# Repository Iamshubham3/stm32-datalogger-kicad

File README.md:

# STM32 Datalogger PCB (KiCad)

This project started from an STM32 dev-board baseline and was extended into a datalogger-oriented PCB.
Main additions: external EEPROM (I2C), LSE crystal for RTC accuracy, and backup cell support to keep RTC running when main power is off.

## What I changed (conversion summary)
- Added I2C EEPROM block (address pins, decoupling, write-protect as applicable)
- Added I2C pull-up resistors sized for 3.3V logic
- Added 32.768 MHz crystal (LSE) for stable RTC timekeeping
- Added backup power cell circuitry (VBAT/RTC domain support)
- Updated connectors/test points for logging/debug (UART/I2C as required)
- Verified ERC/DRC and updated net labels + power domains

## Datalogger use-case
- Logs sensor/measurement data via I2C/SPI/UART peripherals
- Stores samples into EEPROM and timestamps using RTC (battery-backed)

## Tools
- KiCad v8

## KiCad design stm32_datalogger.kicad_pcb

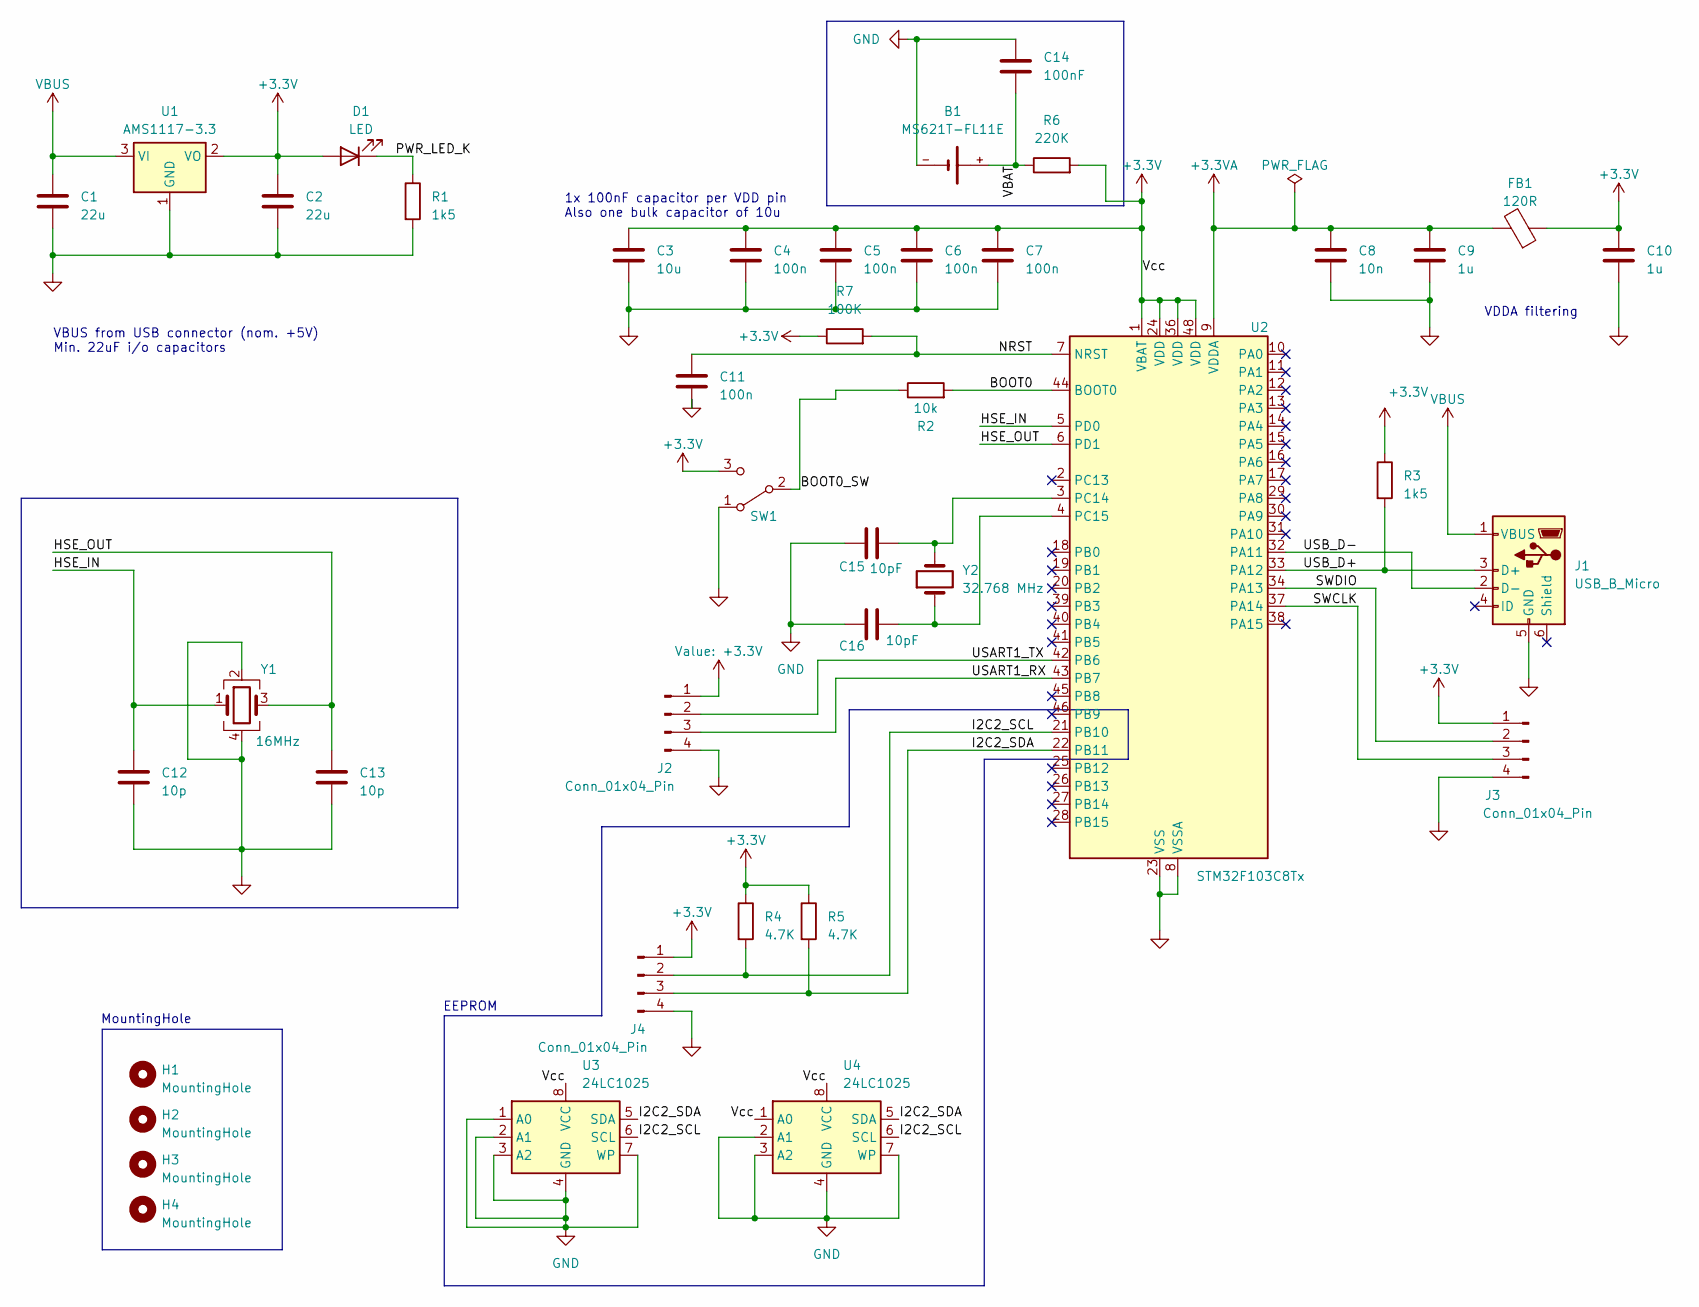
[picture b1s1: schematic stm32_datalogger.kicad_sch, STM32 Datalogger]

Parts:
B1: MS621T-FL11E; MS621FE-FL11E
C1, C2: 22u; C_0805_2012Metric
C3: 10u; C_0603_1608Metric
C4, C5, C6, C7, C11: 100n; C_0402_1005Metric
C8: 10n; C_0402_1005Metric
C9, C10: 1u; C_0402_1005Metric
C12, C13: 10p; C_0402_1005Metric
C14: 100nF; C_0402_1005Metric
C15, C16: 10pF; C_0402_1005Metric
D1: LED; LED_0603_1608Metric
FB1: 120R; L_0603_1608Metric
H1, H2, H3, H4: MountingHole; MountingHole_2.2mm_M2
J1: USB_B_Micro; USB_Micro-B_Wuerth_629105150521
J2, J3, J4: Conn_01x04_Pin; PinHeader_1x04_P2.54mm_Vertical
R1, R3: 1k5; R_0402_1005Metric
R2: 10k; R_0402_1005Metric
R4, R5: 4.7K; R_0402_1005Metric
R6: 220K; R_0402_1005Metric
R7: 100K; R_0402_1005Metric
SW1: SW_SPDT; SW_SPDT_PCM12
U1: AMS1117-3.3; SOT-223-3_TabPin2
U2: STM32F103C8Tx; LQFP-48_7x7mm_P0.5mm
U3, U4: 24LC1025; SOIC-8_3.9x4.9mm_P1.27mm
Y1: 16MHz; Crystal_SMD_3225-4Pin_3.2x2.5mm
Y2: 32.768 MHz; Crystal_SMD_3215-2Pin_3.2x1.5mm

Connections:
+3.3V: C2.1, C3.1, C4.1, C5.1, C6.1, C7.1, C10.1, D1.2 (A), FB1.1, J2.1, J3.1, J4.1, R3.1, R4.1, R5.1, R6.2, R7.1, SW1.3 (C), U1.2 (VO), U2.1 (VBAT), U2.24 (VDD), U2.36 (VDD), U2.48 (VDD), U3.8 (VCC), U4.1 (A0), U4.8 (VCC)
+3.3VA: C8.1, C9.1, FB1.2, U2.9 (VDDA)
/BOOT0: R2.2, U2.44 (BOOT0)
/BOOT0_SW: R2.1, SW1.2 (B)
/HSE_IN: C12.1, U2.5 (PD0), Y1.1
/HSE_OUT: C13.1, U2.6 (PD1), Y1.3
/I2C2_SCL: J4.2, R4.2, U2.21 (PB10), U3.6 (SCL), U4.6 (SCL)
/I2C2_SDA: J4.3, R5.2, U2.22 (PB11), U3.5 (SDA), U4.5 (SDA)
/NRST: C11.1, R7.2, U2.7 (NRST)
/PWR_LED_K: D1.1 (K), R1.1
/SWCLK: J3.3, U2.37 (PA14)
/SWDIO: J3.2, U2.34 (PA13)
/USART1_RX: J2.3, U2.43 (PB7)
/USART1_TX: J2.2, U2.42 (PB6)
/USB_D+: J1.3 (D+), R3.2, U2.33 (PA12)
/USB_D-: J1.2 (D-), U2.32 (PA11)
/VBAT: B1.+, C14.2, R6.1
GND: B1.-, C1.2, C2.2, C3.2, C4.2, C5.2, C6.2, C7.2, C8.2, C9.2, C10.2, C11.2, C12.2, C13.2, C14.1, C15.1, C16.1, J1.5 (GND), J2.4, J3.4, J4.4, R1.2, SW1.1 (A), U1.1 (GND), U2.8 (VSSA), U2.23 (VSS), U2.35 (VSS), U2.47 (VSS), U3.1 (A0), U3.2 (A1), U3.3 (A2), U3.4 (GND), U3.7 (WP), U4.2 (A1), U4.3 (A2), U4.4 (GND), U4.7 (WP), Y1.2, Y1.4
unnamed: C15.2, U2.3 (PC14), Y2.2
unnamed: C16.2, U2.4 (PC15), Y2.1
VBUS: C1.1, J1.1 (VBUS), U1.3 (VI)

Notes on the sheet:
1x 100nF capacitor per VDD pin Also one bulk capacitor of 10u
VBUS from USB connector (nom. +5V) Min. 22uF i/o capacitors
EEPROM
VDDA filtering
MountingHole

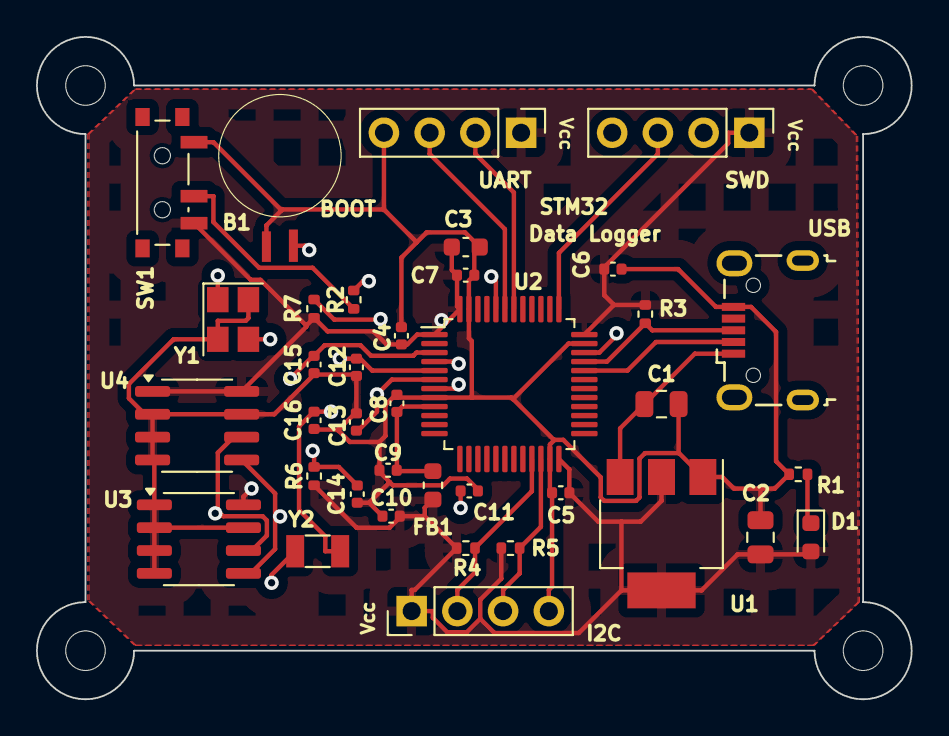
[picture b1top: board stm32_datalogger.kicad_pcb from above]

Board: 4 copper layers, 48.6 x 36.8 mm, 41 parts (0 on the bottom side), 21 nets.

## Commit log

2026-01-12 Initial commit: KiCad STM32 datalogger project
2026-01-12 Ignore assets directory
2026-01-12 Initialize README with project details and usage
    Added project overview and conversion summary for STM32 Datalogger PCB.
2026-01-12 Fix typo in crystal frequency for RTC timekeeping
2026-01-12 Update KiCad version in README
